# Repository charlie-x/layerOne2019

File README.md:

View this project on [CADLAB.io](https://cadlab.io/project/22870). 

# layerOne2019
LayerOne 2019 conference www.layerone.org

firmware - folder for kitbadge L1 LOGO see notes in there, 

MOSI, MISO, SCK, VCC, RST, GND

MOSI is closest to top of badge.

firmware for esp32 camera board

https://github.com/m5stack

https://www.youtube.com/watch?v=pfQ5VgcnJhg

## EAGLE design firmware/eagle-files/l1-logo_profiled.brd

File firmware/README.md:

# linux
  sudo apt-get install gcc-avr binutils-avr avr-libc -y

# For programming
  sudo apt-get install avrdude

# OSX
  brew tap osx-cross/avr
  brew install avr-libc
  
# For programming
  brew install avrdude --with-usb

# Windows
  Install AVR studio or Atmel Studio , load project, compile and program

# OSX / Linux
  avr-gcc -g -Os -mmcu=attiny2313a larson.c -DF_CPU=8000000  -o larson.elf
  avr-objcopy -j .text -j .data -O ihex larson.elf larson.hex

  # Fuses are default

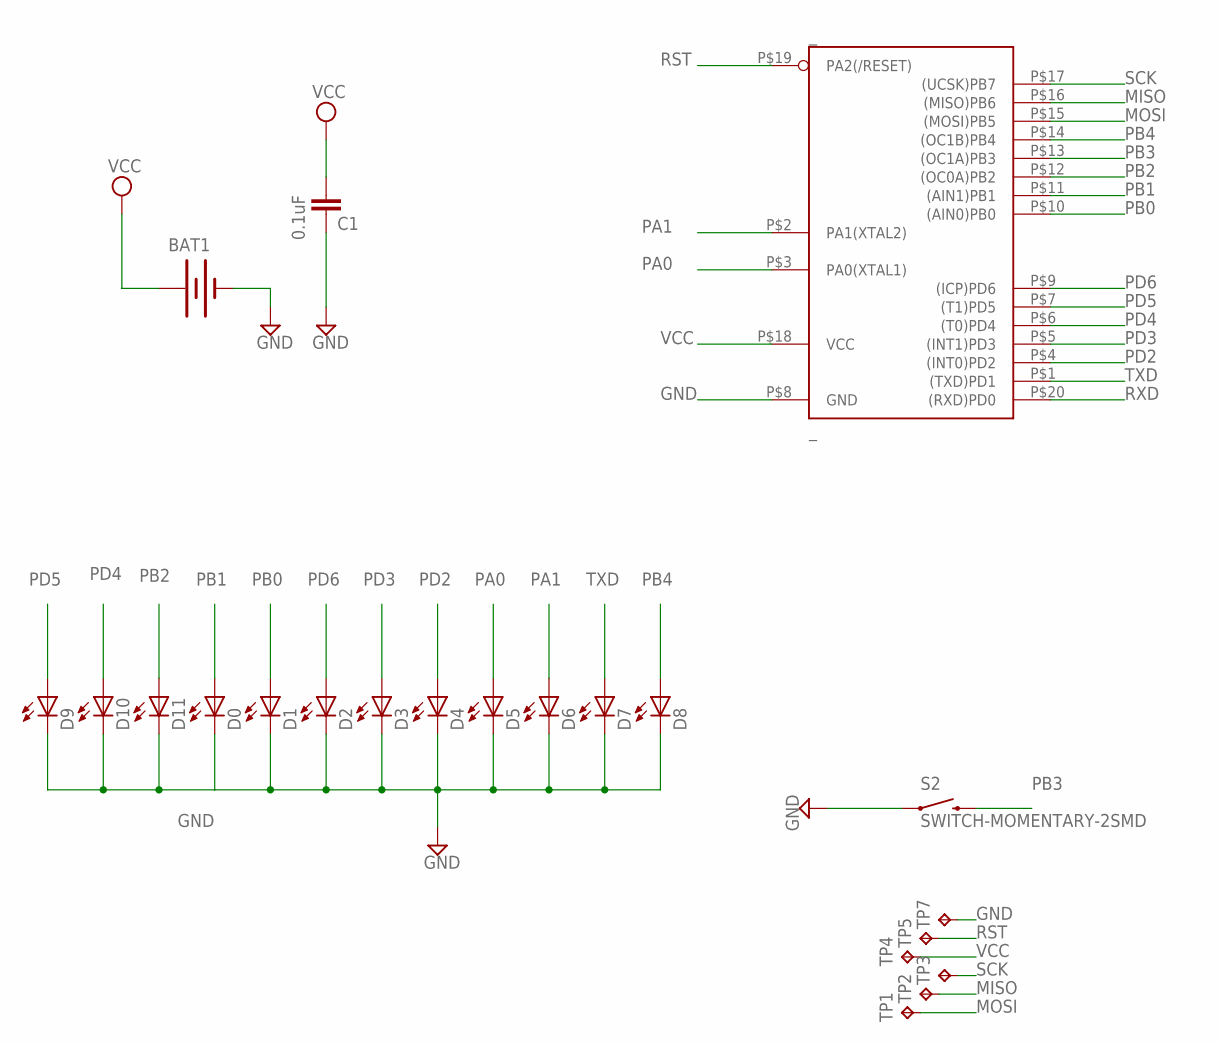
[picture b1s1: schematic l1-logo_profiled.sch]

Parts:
BAT1: SPARKFUN_BATTERYSPARKFUN_BATTCOMM_20MM_LINX; SPARKFUN_BATTCOM_20MM_LINX
C1: 0.1uF; 0805
D0, D1, D2, D3, D4, D5, D6, D7, D8, D9, D10, D11: SPARKFUN_LED1206; SPARKFUN_LED-1206
S2: SWITCH-MOMENTARY-2SMD; TACTILE_SWITCH_SMD
TP1, TP2, TP3, TP4, TP5, TP7: TPTP18R; TP18R
_: _; MLF20

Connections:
GND: BAT1.2 (-), C1.2, D0.C, D1.C, D2.C, D3.C, D4.C, D5.C, D6.C, D7.C, D8.C, D9.C, D10.C, D11.C, S2.1, TP7.TP, _.P$8 (GND)
MISO: TP2.TP, _.P$16 ((MISO)PB6)
MOSI: TP1.TP, _.P$15 ((MOSI)PB5)
PA0: D5.A, _.P$3 (PA0(XTAL1))
PA1: D6.A, _.P$2 (PA1(XTAL2))
PB0: D1.A, _.P$10 ((AIN0)PB0)
PB1: D0.A, _.P$11 ((AIN1)PB1)
PB2: D11.A, _.P$12 ((OC0A)PB2)
PB3: S2.3 (2), _.P$13 ((OC1A)PB3)
PB4: D8.A, _.P$14 ((OC1B)PB4)
PD2: D4.A, _.P$4 ((INT0)PD2)
PD3: D3.A, _.P$5 ((INT1)PD3)
PD4: D10.A, _.P$6 ((T0)PD4)
PD5: D9.A, _.P$7 ((T1)PD5)
PD6: D2.A, _.P$9 ((ICP)PD6)
RST: TP5.TP, _.P$19 (PA2(/RESET))
RXD: _.P$20 ((RXD)PD0)
SCK: TP3.TP, _.P$17 ((UCSK)PB7)
TXD: D7.A, _.P$1 ((TXD)PD1)
VCC: BAT1.1 (+), C1.1, TP4.TP, _.P$18 (VCC)

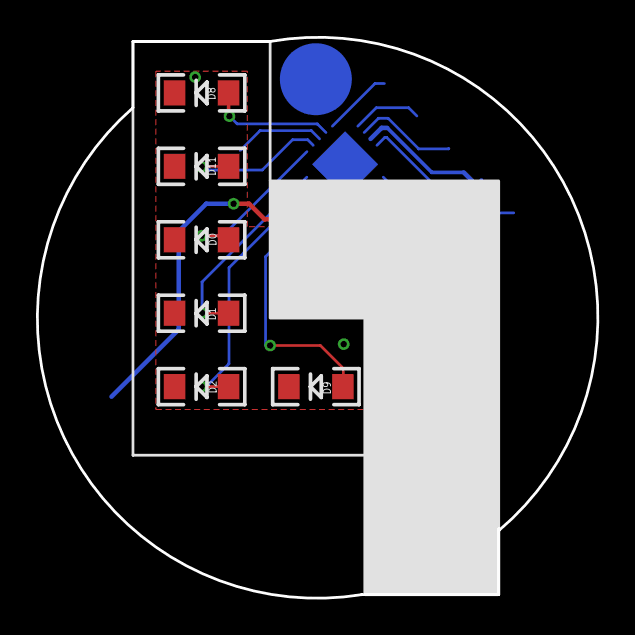
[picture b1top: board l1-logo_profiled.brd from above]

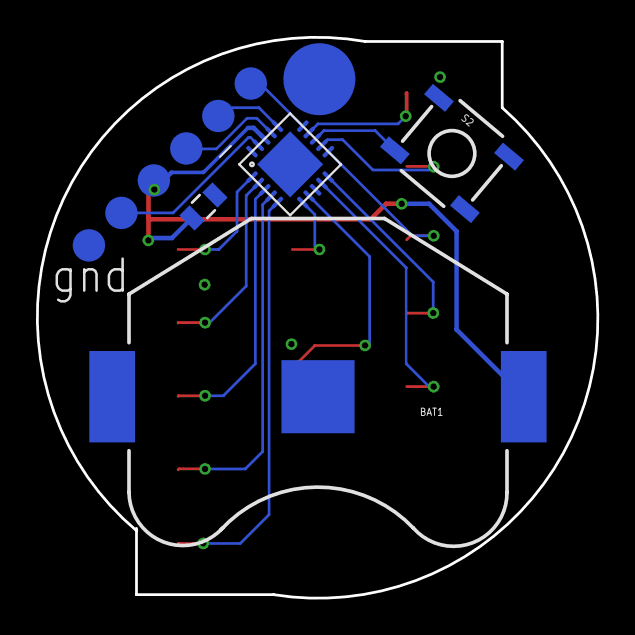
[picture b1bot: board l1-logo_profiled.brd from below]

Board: 2 copper layers, 31.1 x 31.2 mm, 22 parts (10 on the bottom side), 19 nets.

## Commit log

2019-05-25 kitbadge mini l1 logo firmware
    binary counter, larson.c is the main file. atmel studio and avr studio added.
    program is MOSI, MISO, SCK, VCC, RST,GND
    MOSI is closest to top of badge.
2019-05-25 added eagle files and pdfs for board and schematic
2019-05-25 code for the l1 badge, attiny2313 avr studio/atmel studio
2019-05-26 Add files via upload
    added cylon mode
2020-05-05 Backlink to CADLAB.io has been added.
